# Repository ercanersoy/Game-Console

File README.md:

# Game Console

A Uzebox based game console

Some changes applied by Ercan Ersoy.

This project licensed under GNU GPL v3.

## Description

This hardware is Uzebox hardware without unused items.

Formats of the hardware files are KiCAD formats.

## Reference

[Uzebox](https://uzebox.org/)

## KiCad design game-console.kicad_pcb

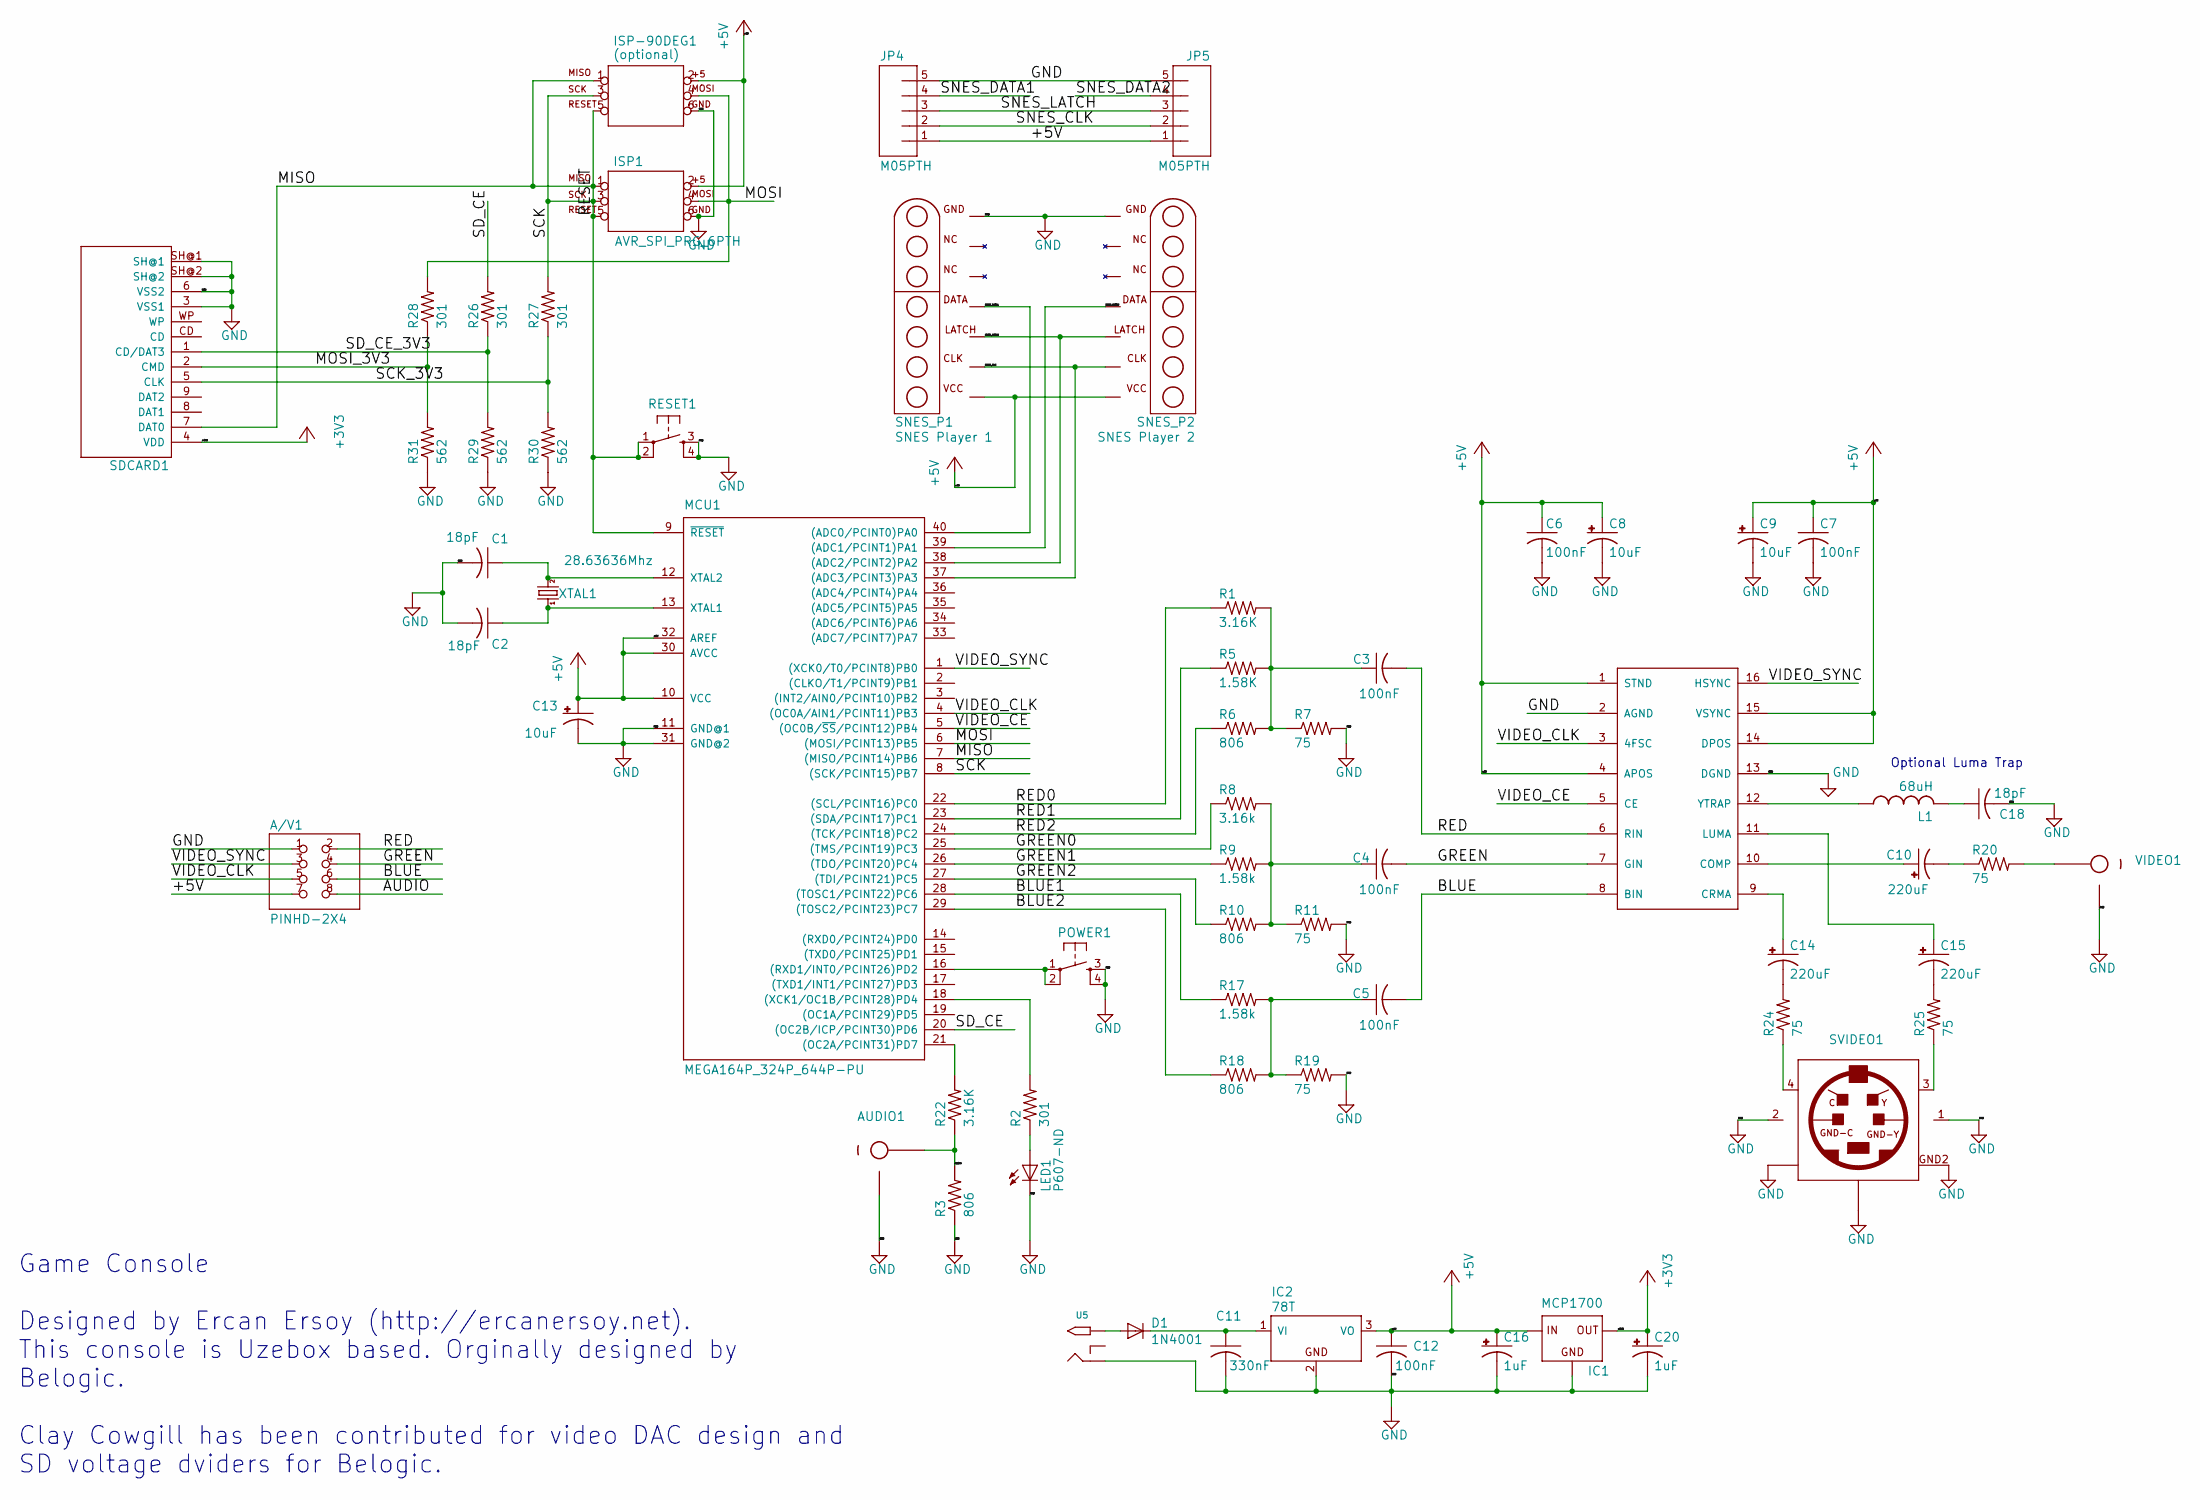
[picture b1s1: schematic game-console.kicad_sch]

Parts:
A/V1: PINHD-2X4; 2X04
AD725: AD725; SO16W
AUDIO1: RCA
C1, C2, C18: 18pF; C025-025X050
C3, C4, C5, C6, C7, C12: 100nF; C025-025X050
C8, C9, C13: 10uF; E2,5-6
C10, C14, C15: 220uF; E2,5-6
C11: 330nF; C025-025X050
C16, C20: 1uF; E2,5-6
D1: 1N4001; DO41-10
IC1: MCP1700; TO92-INLINE
IC2: 78T; TO220H
ISP1: AVR_SPI_PRG_6PTH; 2X3
ISP-90DEG1: (optional); 2X3
JP4, JP5: M05PTH; 1X05
L1: 68uH; 6000-XXXX-RC
LED1: P607-ND; LED3MM
MCU1: MEGA164P_324P_644P-PU; DIL40
POWER1: USER; TACTILE-PTH
R1, R22: 3.16K; 0207_10
R2, R26, R27, R28: 301; 0207_10
R3, R6, R10, R18: 806; 0207_10
R5: 1.58K; 0207_10
R7, R11, R19, R20, R24, R25: 75; 0207_10
R8: 3.16k; 0207_10
R9, R17: 1.58k; 0207_10
R29, R30, R31: 562; 0207_10
RESET1: RESET; TACTILE-PTH
SDCARD1: SD_CARD_SOCKET4UCON; SDCARD_4UCONN
SNES_P1: SNES Player 1; SNES_CONNECTOR
SNES_P2: SNES Player 2; SNES_CONNECTOR
SVIDEO1: S-VIDEO OUT; MINIDIN4
U5: DC IN; PJ-102A
VIDEO1: RCA
XTAL1: 28.63636Mhz; HC49_S

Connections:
+3V3: C20.+, IC1.3 (OUT), SDCARD1.4 (VDD)
+5V: A/V1.7, AD725.1 (STND), AD725.4 (APOS), AD725.14 (DPOS), AD725.15 (VSYNC), C6.1, C7.1, C8.+, C9.+, C12.1, C13.+, C16.+, IC1.2 (IN), IC2.3 (VO), ISP1.2, ISP-90DEG1.2, JP4.1, JP5.1, MCU1.10 (VCC), MCU1.30 (AVCC), MCU1.32 (AREF), SNES_P1.P$8 (VCC), SNES_P2.P$8 (VCC)
/AUDIO: A/V1.8, AUDIO1.SIG, R3.2, R22.1
/BLUE: A/V1.6, AD725.8 (BIN), C5.2
/BLUE1: MCU1.28 ((TOSC1/PCINT22)PC6), R17.1
/BLUE2: MCU1.29 ((TOSC2/PCINT23)PC7), R18.1
/GREEN: A/V1.4, AD725.7 (GIN), C4.2
/GREEN0: MCU1.25 ((TMS/PCINT19)PC3), R8.1
/GREEN1: MCU1.26 ((TDO/PCINT20)PC4), R9.1
/GREEN2: MCU1.27 ((TDI/PCINT21)PC5), R10.1
/MOSI: ISP1.4, ISP-90DEG1.4, MCU1.6 ((MOSI/PCINT13)PB5), R28.2
/MOSI_3V3: R28.1, R31.2, SDCARD1.2 (CMD)
/RED: A/V1.2, AD725.6 (RIN), C3.2
/RED0: MCU1.22 ((SCL/PCINT16)PC0), R1.1
/RED1: MCU1.23 ((SDA/PCINT17)PC1), R5.1
/RED2: MCU1.24 ((TCK/PCINT18)PC2), R6.1
/SCK_3V3: R27.1, R30.2, SDCARD1.5 (CLK)
/SD_CE: MCU1.20 ((OC2B/ICP/PCINT30)PD6), R26.2
/SD_CE_3V3: R26.1, R29.2, SDCARD1.1 (CD/DAT3)
/SNES_CLK: JP4.2, JP5.2, MCU1.37 ((ADC3/PCINT3)PA3), SNES_P1.P$9 (CLK), SNES_P2.P$9 (CLK)
/SNES_DATA1: JP4.4, MCU1.40 ((ADC0/PCINT0)PA0), SNES_P1.P$11 (DATA)
/SNES_DATA2: JP5.4, MCU1.39 ((ADC1/PCINT1)PA1), SNES_P2.P$11 (DATA)
/SNES_LATCH: JP4.3, JP5.3, MCU1.38 ((ADC2/PCINT2)PA2), SNES_P1.P$10 (LATCH), SNES_P2.P$10 (LATCH)
/VIDEO_CE: AD725.5 (CE), MCU1.5 ((OC0B/~SS/PCINT12)PB4)
/VIDEO_CLK: A/V1.5, AD725.3 (4FSC), MCU1.4 ((OC0A/AIN1/PCINT11)PB3)
/VIDEO_SYNC: A/V1.3, AD725.16 (HSYNC), MCU1.1 ((XCK0/T0/PCINT8)PB0)
GND: A/V1.1, AD725.2 (AGND), AD725.13 (DGND), AUDIO1.GND, C1.2, C2.2, C6.2, C7.2, C8.-, C9.-, C11.2, C12.2, C13.-, C16.-, C18.2, C20.-, IC1.1 (GND), IC2.2 (GND), ISP1.6, ISP-90DEG1.6, JP4.5, JP5.5, LED1.K (C), MCU1.11 (GND@1), MCU1.31 (GND@2), POWER1.3, POWER1.4, R3.1, R7.2, R11.2, R19.2, R29.1, R30.1, R31.1, RESET1.3, RESET1.4, SDCARD1.3 (VSS1), SDCARD1.6 (VSS2), SDCARD1.SH@1, SDCARD1.SH@2, SNES_P1.P$14 (GND), SNES_P2.P$14 (GND), SVIDEO1.1 (GND-Y), SVIDEO1.2 (GND-C), SVIDEO1.GND1, SVIDEO1.GND2, SVIDEO1.GND3, U5.RING, VIDEO1.GND
unnamed: AD725.9 (CRMA), C14.+
unnamed: AD725.10 (COMP), C10.+
unnamed: AD725.11 (LUMA), C15.+
unnamed: AD725.12 (YTRAP), L1.1
unnamed: C1.1, MCU1.12 (XTAL2), XTAL1.2
unnamed: C2.1, MCU1.13 (XTAL1), XTAL1.1
unnamed: C3.1, R1.2, R5.2, R6.2, R7.1
unnamed: C4.1, R8.2, R9.2, R10.2, R11.1
unnamed: C5.1, R17.2, R18.2, R19.1
unnamed: C10.-, R20.1
unnamed: C11.1, D1.C, IC2.1 (VI)
unnamed: C14.-, R24.2
unnamed: C15.-, R25.2
unnamed: C18.1, L1.2
unnamed: D1.A, U5.TIP
unnamed: LED1.A, R2.1
unnamed: MCU1.16 ((RXD1/INT0/PCINT26)PD2), POWER1.1, POWER1.2
unnamed: MCU1.18 ((XCK1/OC1B/PCINT28)PD4), R2.2
unnamed: MCU1.21 ((OC2A/PCINT31)PD7), R22.2
unnamed: R20.2, VIDEO1.SIG
unnamed: R24.1, SVIDEO1.4 (C)
unnamed: R25.1, SVIDEO1.3 (Y)

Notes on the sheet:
Optional Luma Trap
Game Console Designed by Ercan Ersoy (http://ercanersoy.net). This console is Uzebox based. Orginally designed by Belogic. Clay Cowgill has been contributed for video DAC design and SD voltage dviders for Belogic.

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
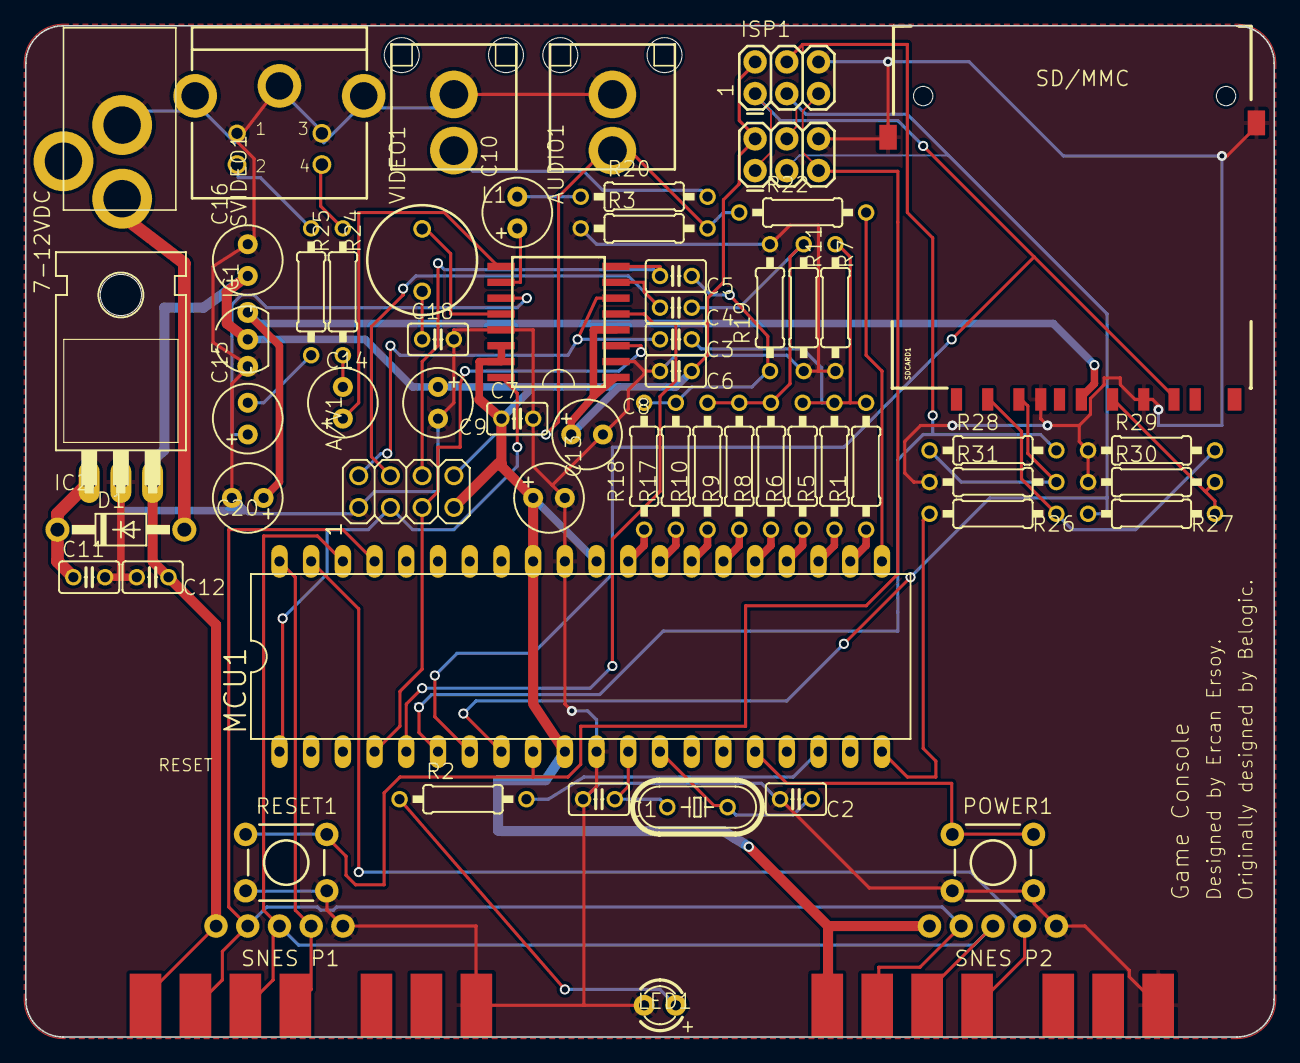
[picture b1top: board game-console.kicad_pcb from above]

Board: 2 copper layers, 100.0 x 81.0 mm, 63 parts (0 on the bottom side), 52 nets.

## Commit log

2021-01-30 Initial hardware files
2021-11-01 Some important changes
    * Update README.md file as remove wrong copyright information and
    add information of applied changes
    * Update fp-lib-table as update library name from old name to new
    name
2024-08-04 Some updates
    * Remove old names
    * Update format of project files as new format
    * Remove old and garbage files
    * Update .gitignore
2024-08-04 Update README.md
    Update reference link
